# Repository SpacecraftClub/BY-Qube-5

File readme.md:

# BY-QUBE-5
</img></img><br>
The fith itteration of BYU Spacecraft's PocketQube project. Based on the success of BY-QUBE-4 we aim to itterate and improve on our previous designs.
## Preamble
For the last 4 years, undergraduate students have participated in the BY-QUBE 1p pocketqube program. 
### BY-QUBE-4
</img></img>
## Improvements for this year
### Improved board stackup design
Using a blade design for interfacing the boards into eachother rather than crimped wire interfaces. This will increase durability, simplify the assembly process, and allow for easy swapping of subsystems as needed.

</img></img>
</img></img>
</img>

## Design Reviews
[Nov 3rd 2026](markdown/Design%20Review/Nov-3-2026.md)

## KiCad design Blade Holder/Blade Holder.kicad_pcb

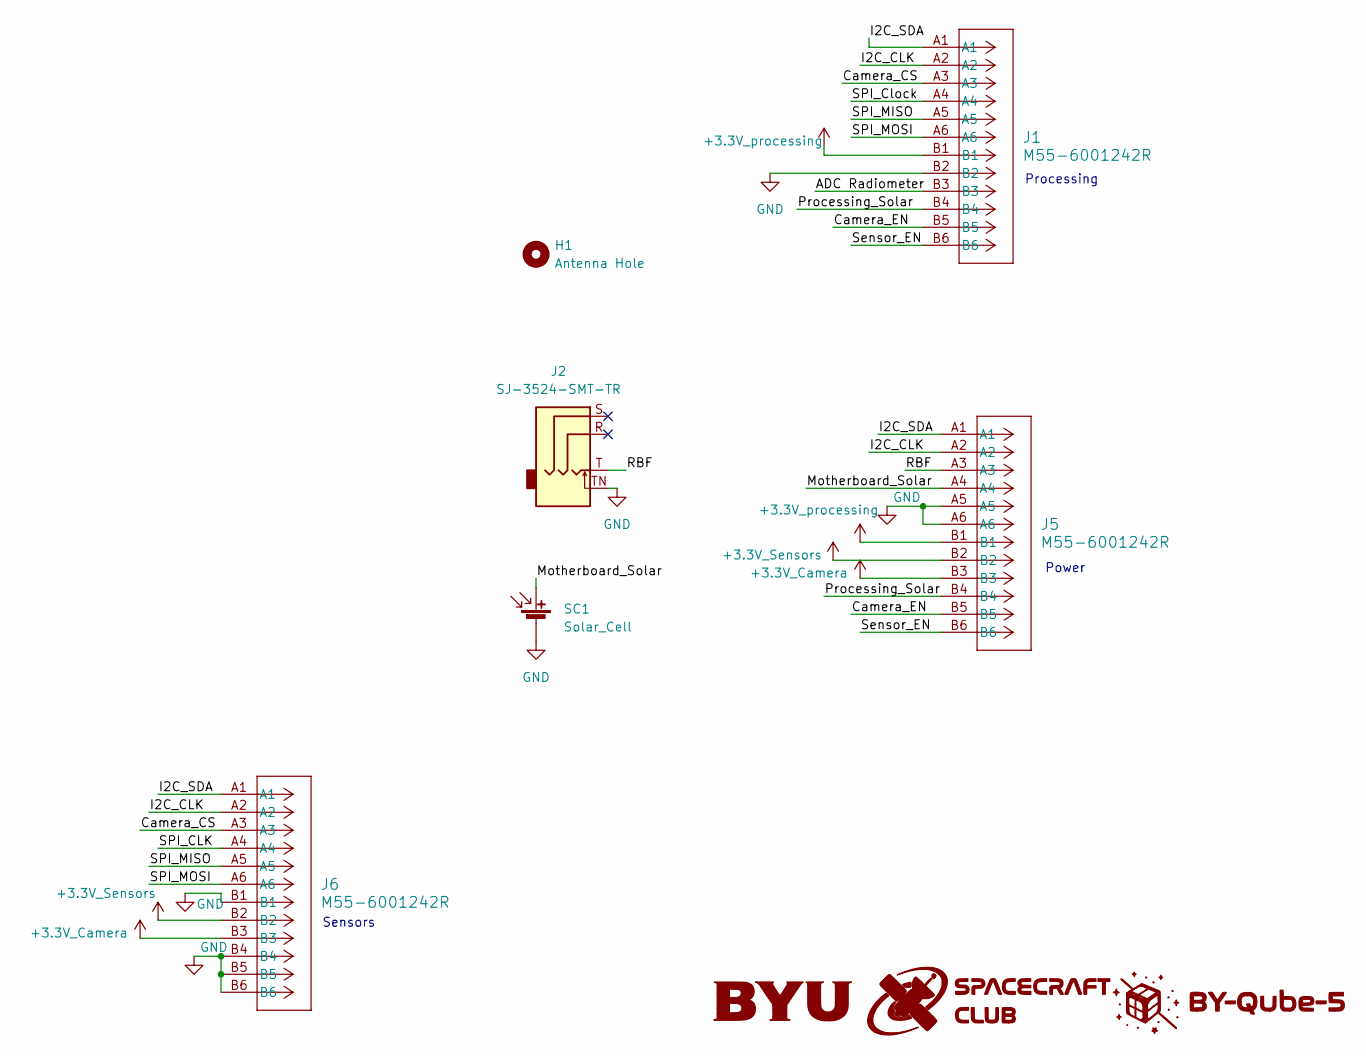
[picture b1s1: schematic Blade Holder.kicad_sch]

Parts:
G1: LOGO; silkLogo_small
H1: Antenna Hole; MountingHole_2.2mm_M2
J1, J5, J6: M55-6001242R; CONN_M55-6001242R_HRW
J2: SJ-3524-SMT-TR; Jack_3.5mm_CUI_SJ-3524-SMT_Horizontal
SC1: Solar_Cell; SM101K12L

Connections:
+3.3V_Camera: J5.B3, J6.B3
+3.3V_Sensors: J5.B2, J6.B2
+3.3V_processing: J1.B1, J5.B1
/ADC Radiometer: J1.B3
/Camera_CS: J1.A3, J6.A3
/Camera_EN: J1.B5, J5.B5
/I2C_CLK: J1.A2, J5.A2, J6.A2
/I2C_SDA: J1.A1, J5.A1, J6.A1
/Motherboard_Solar: J5.A4, SC1.1 (+)
/Processing_Solar: J1.B4, J5.B4
/RBF: J2.T, J5.A3
/SPI_CLK: J6.A4
/SPI_Clock: J1.A4
/SPI_MISO: J1.A5, J6.A5
/SPI_MOSI: J1.A6, J6.A6
/Sensor_EN: J1.B6, J5.B6
GND: J1.B2, J2.TN, J5.A5, J5.A6, J6.B1, J6.B4, J6.B5, J6.B6, SC1.2 (-)

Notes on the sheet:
Sensors
Processing
Power

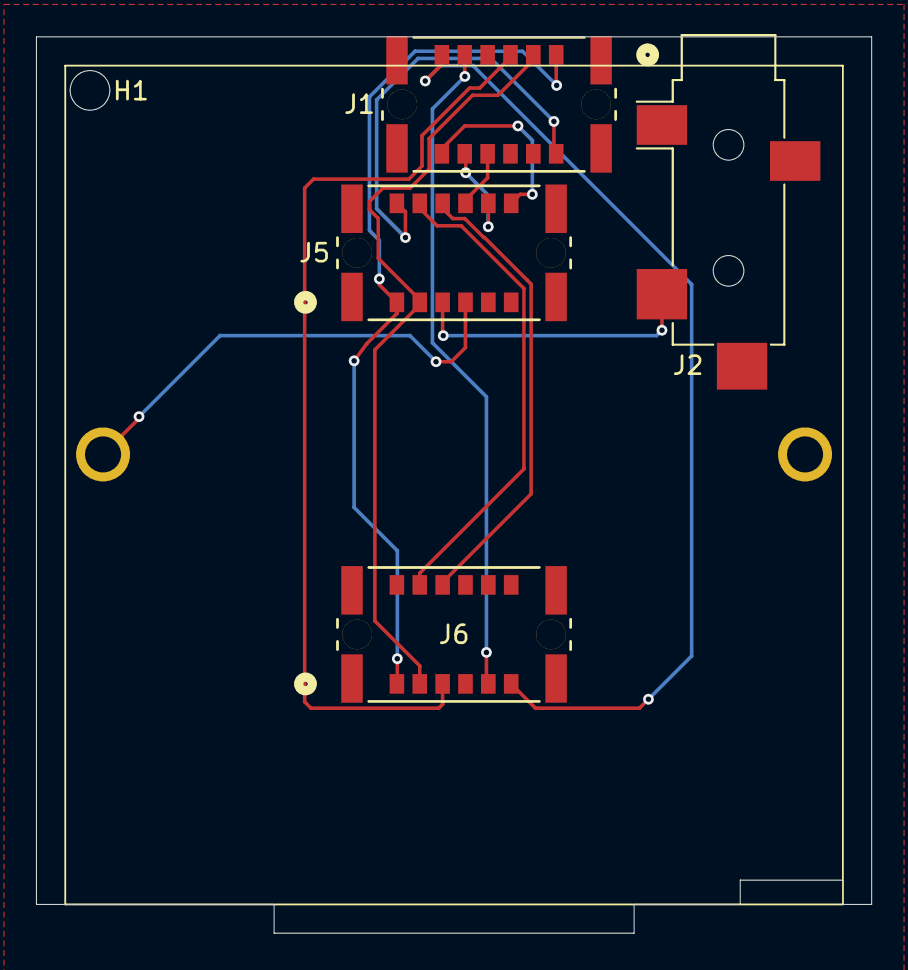
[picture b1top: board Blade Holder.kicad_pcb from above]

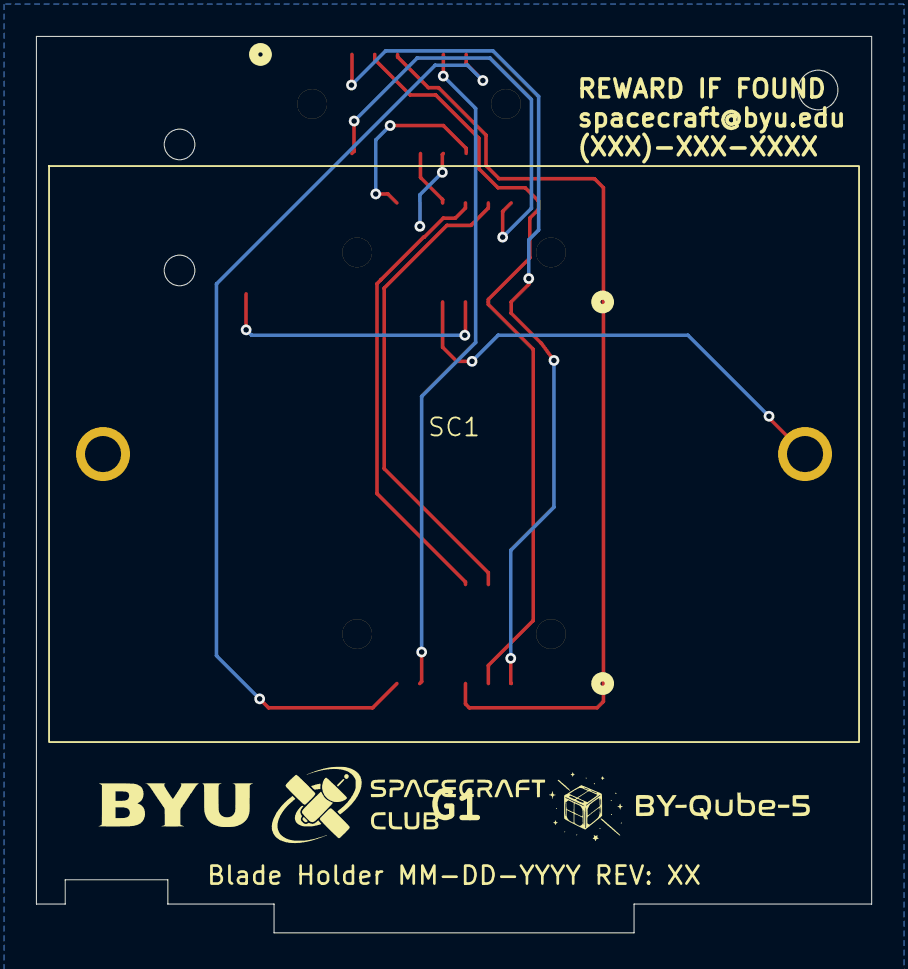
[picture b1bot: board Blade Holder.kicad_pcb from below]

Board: 2 copper layers, 46.4 x 49.8 mm, 7 parts (2 on the bottom side), 14 nets.

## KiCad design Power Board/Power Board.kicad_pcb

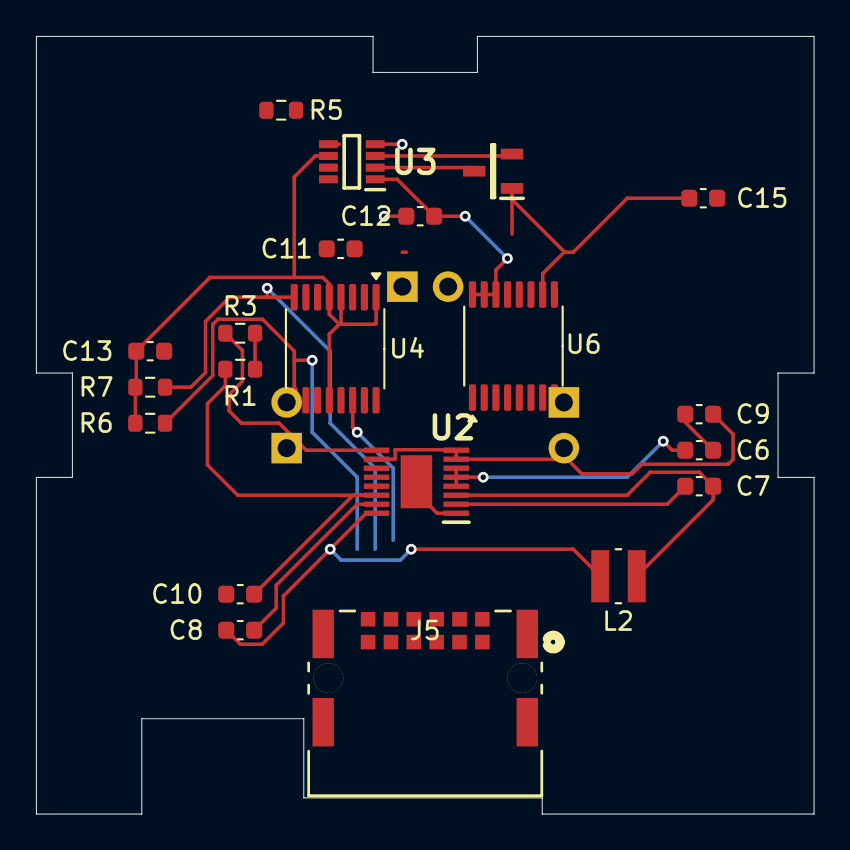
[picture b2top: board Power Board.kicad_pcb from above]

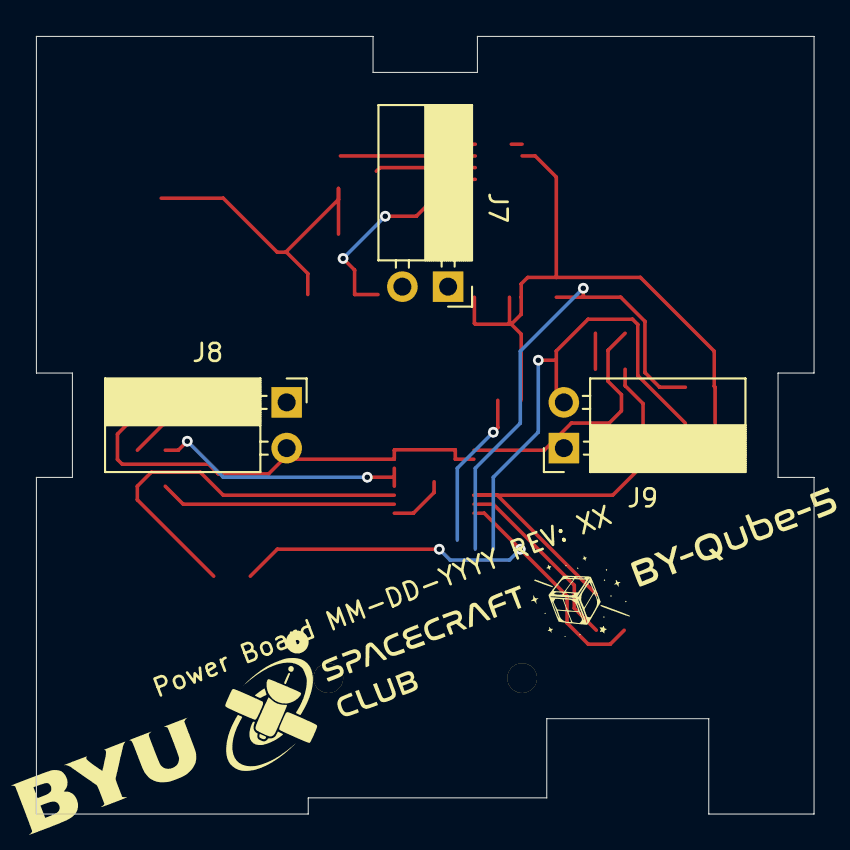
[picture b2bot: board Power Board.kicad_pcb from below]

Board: 2 copper layers, 43.2 x 43.2 mm, 25 parts (4 on the bottom side), 19 nets.

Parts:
C6, C13, C15: 1uF; C_0603_1608Metric
C7, C8: 22nF; C_0603_1608Metric
C9, C10: 4.7uF; C_0603_1608Metric
C11, C12: 1 uF; C_0603_1608Metric
G1: LOGO; silkLogo
J5: M55-7101242R; CONN_M55-7101242R_HRW
J7, J8, J9: Conn_01x02; PinSocket_1x02_P2.54mm_Horizontal
L2: 6.8uH; IND_EPL3015-682MLC
Q1: PNP; SOT96P237X111-3N
R1, R3: 200k; R_0603_1608Metric
R5: 1.3k; R_0603_1608Metric
R6, R7: 10K; R_0603_1608Metric
U2: LTC3130EMSE#PBF; LTC3130
U3: LTC4056ETS8-4.2#TRMPBF; LTC4056ETS8-4.2
U4, U6: INA260; TSSOP-16_4.4x5mm_P0.65mm

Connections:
/SCL: R6.2, U4.9 (SCL), U6.9 (SCL)
/SDA: R7.2, U4.8 (SDA), U6.8 (SDA)
/Vcharge+: C10.1, R1.1, U2.14 (VOUT), U6.1 (IN+), U6.2 (IN+), U6.3 (IN+), U6.12 (VBUS)
/Vcharge-: C12.1, U3.1 (VCC), U6.14 (IN-), U6.15 (IN-), U6.16 (IN-)
/Vout+: C13.1, C15.1, Q1.1 (C), R6.1, R7.1, U3.6 (BAT), U4.1 (IN+), U4.2 (IN+), U4.3 (IN+), U4.4 (A1), U4.5 (A0), U4.10 (VS), U4.12 (VBUS), U6.10 (VS)
/Vout-: U4.14 (IN-), U4.15 (IN-), U4.16 (IN-)
/Vsolar: C6.1, U2.4 (PVIN), U2.5 (VIN), U2.6 (RUN)
GND: C6.2, C9.2, C10.2, C11.2, C12.2, C13.2, C15.2, R5.2, U2.1 (GND_1), U2.11 (MODE), U2.12 (EXTVCC), U2.17 (GND_2), U3.4 (GND), U4.6 (GND), U4.11 (GND), U6.4 (A1), U6.5 (A0), U6.6 (GND), U6.11 (GND)
unnamed: Q1.2 (B), U3.3 (DRIVE)
unnamed: Q1.3 (E), U3.2 (ISENSE)
unnamed: R1.2, R3.1
unnamed: C7.1, U2.2 (BST1)
unnamed: C8.2, U2.15 (BST2)
unnamed: C9.1, U2.7 (VCC), U2.8 (MPPC), U2.10 (VS1/ILIM)
unnamed: C7.2, L2.1, U2.3 (SW1)
unnamed: C8.1, L2.2, U2.16 (SW2)
unnamed: R3.2, U2.9 (VS2/FB)
unnamed: R5.1, U3.5 (PROG)
unnamed: C11.1, U3.7 (TIMER/~SHDN)
